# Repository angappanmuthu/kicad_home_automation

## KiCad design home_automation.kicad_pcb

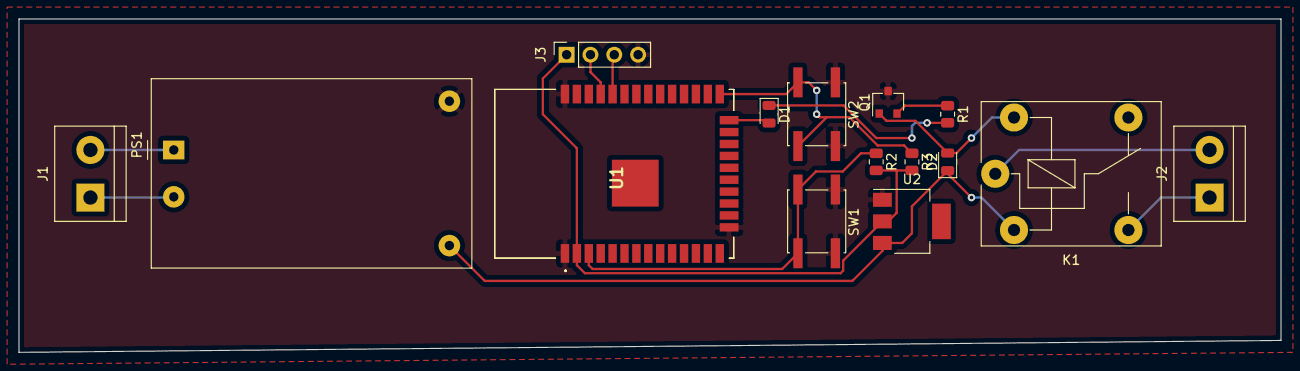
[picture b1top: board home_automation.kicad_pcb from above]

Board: 2 copper layers, 134.6 x 35.6 mm, 15 parts (0 on the bottom side), 15 nets.

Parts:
D1: LED; LED_0805_2012Metric
D2: 1N4001; D_0805_2012Metric
J1, J2: Screw_Terminal_01x02; TerminalBlock_bornier-2_P5.08mm
J3: Conn_01x04_Male; PinSocket_1x04_P2.54mm_Vertical
K1: FINDER-36.11; Relay_SPDT_Finder_36.11
PS1: HLK-PM01; Converter_ACDC_HiLink_HLK-PMxx
Q1: BC547; SC-59
R1, R2, R3: R; R_0805_2012Metric
SW1, SW2: SW_Push; SW_SPST_EVQQ2
U1: ESP32-WROOM-32; ESPWROOM32D
U2: AMS1117-3.3; SOT-223

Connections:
3V: J3.1, R2.2, R3.2, U1.2, U2.2
+5V: D2.1, K1.A1, PS1.4, U2.3
GND: J3.4, PS1.3, Q1.3, SW1.1, SW2.1, U1.1, U1.15, U1.38, U2.1
IN1: D1.2, U1.24
unnamed: D1.1, R1.2
unnamed: D2.2, K1.A2, Q1.1
unnamed: J1.1, PS1.2
unnamed: J1.2, PS1.1
unnamed: J2.1, K1.14
unnamed: J2.2, K1.11
unnamed: Q1.2, R1.1
unnamed: R2.1, SW1.2, U1.3
unnamed: R3.1, SW2.2, U1.25
RX: J3.3, U1.34
TX: J3.2, U1.35
